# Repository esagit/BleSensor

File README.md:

# BLE Sensor Module
BLE sensor module development version for different sensors

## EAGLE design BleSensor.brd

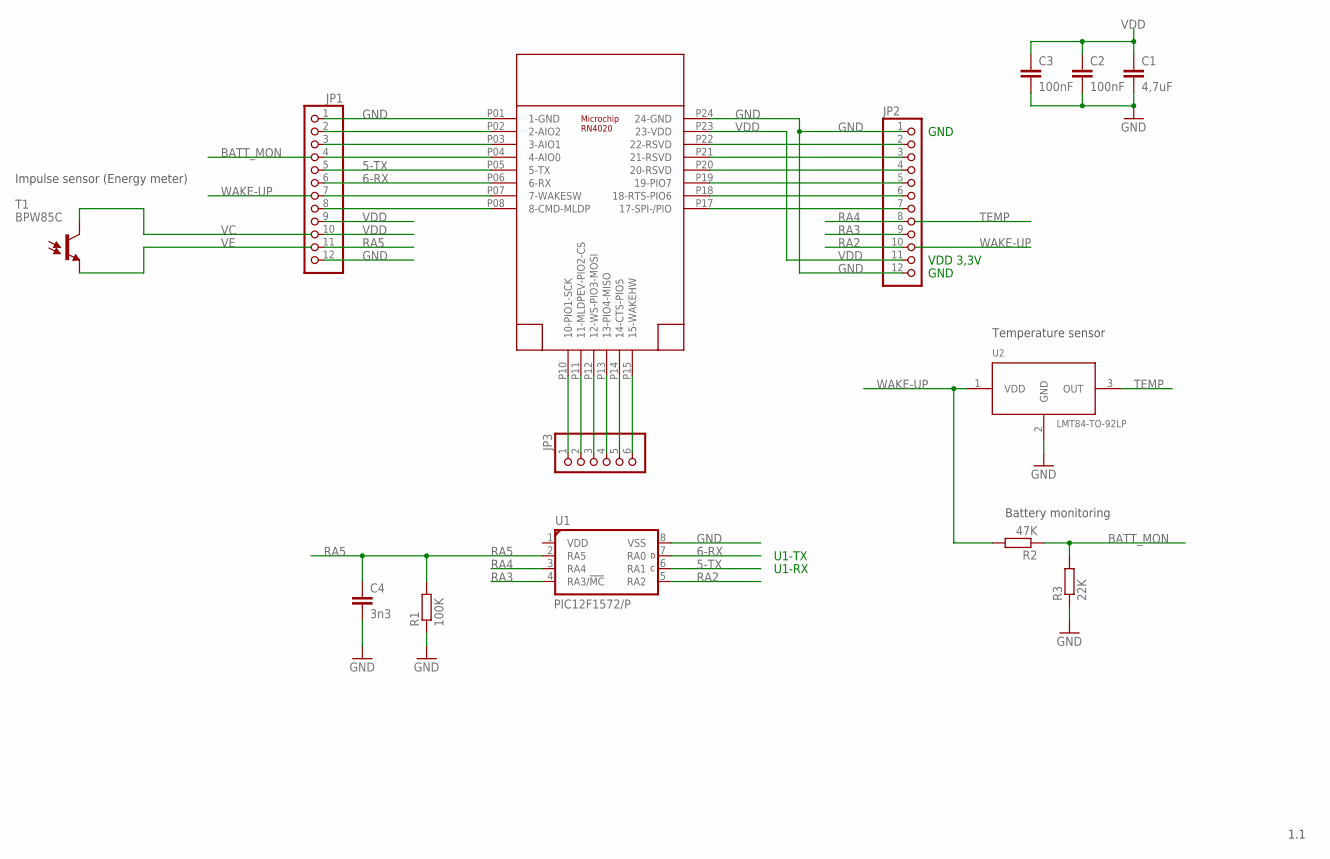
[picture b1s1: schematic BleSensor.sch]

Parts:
C1: 4,7uF; C2.5-3
C2, C3: 100nF; C1206
C4: 3n3; C1206
JP1, JP2: PINHD-1X12; 1X12
JP3: PINHD-1X6; 1X06
R1: 100K; M1206
R2: 47K; M1206
R3: 22K; M1206
T1: BPW85C; LED3MM
U1: PIC12F1572/P; DIL8-P
U2: LMT84-TO-92LP; TO92-LP
U$1: RN4020; RN4020SMD

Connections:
5-TX: JP1.5, U1.6 (RA1), U$1.P05 (5-TX)
6-RX: JP1.6, U1.7 (RA0), U$1.P06 (6-RX)
BATT_MON: JP1.4, R2.1, R3.2, U$1.P04 (4-AIO0)
GND: C1.2, C2.2, C3.2, C4.2, JP1.1, JP1.12, JP2.1, JP2.12, R1.1, R3.1, U1.8 (VSS), U2.2 (GND), U$1.P01 (1-GND), U$1.P24 (24-GND)
unnamed: JP1.8, U$1.P08 (8-CMD-MLDP)
unnamed: JP2.2, U$1.P22 (22-RSVD)
unnamed: JP2.3, U$1.P21 (21-RSVD)
unnamed: JP2.4, U$1.P20 (20-RSVD)
unnamed: JP2.5, U$1.P19 (19-PIO7)
unnamed: JP2.6, U$1.P18 (18-RTS-PIO6)
unnamed: JP2.7, U$1.P17 (17-SPI-/PIO)
unnamed: JP1.2, U$1.P02 (2-AIO2)
unnamed: JP1.3, U$1.P03 (3-AIO1)
unnamed: JP3.1, U$1.P10 (10-PIO1-SCK)
unnamed: JP3.2, U$1.P11 (11-MLDPEV-PIO2-CS)
unnamed: JP3.3, U$1.P12 (12-WS-PIO3-MOSI)
unnamed: JP3.4, U$1.P13 (13-PIO4-MISO)
unnamed: JP3.5, U$1.P14 (14-CTS-PIO5)
unnamed: JP3.6, U$1.P15 (15-WAKEHW)
RA2: JP1.7, JP2.10, U1.5 (RA2), U$1.P07 (7-WAKESW)
RA3: JP2.9, U1.4 (RA3/!MC!)
RA4: JP2.8, U1.3 (RA4)
RA5: C4.1, JP1.11, R1.2, U1.2 (RA5)
TEMP: U2.3 (OUT)
VC: T1.K (C)
VDD: C1.1, C2.1, C3.1, JP1.9, JP1.10, JP2.11, U$1.P23 (23-VDD)
VE: T1.A (E)
WAKE-UP: R2.2, U2.1 (VDD)

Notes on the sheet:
GND
VDD 3,3V
U1-TX
U1-RX
1.1
Temperature sensor
Impulse sensor (Energy meter)
Battery monitoring

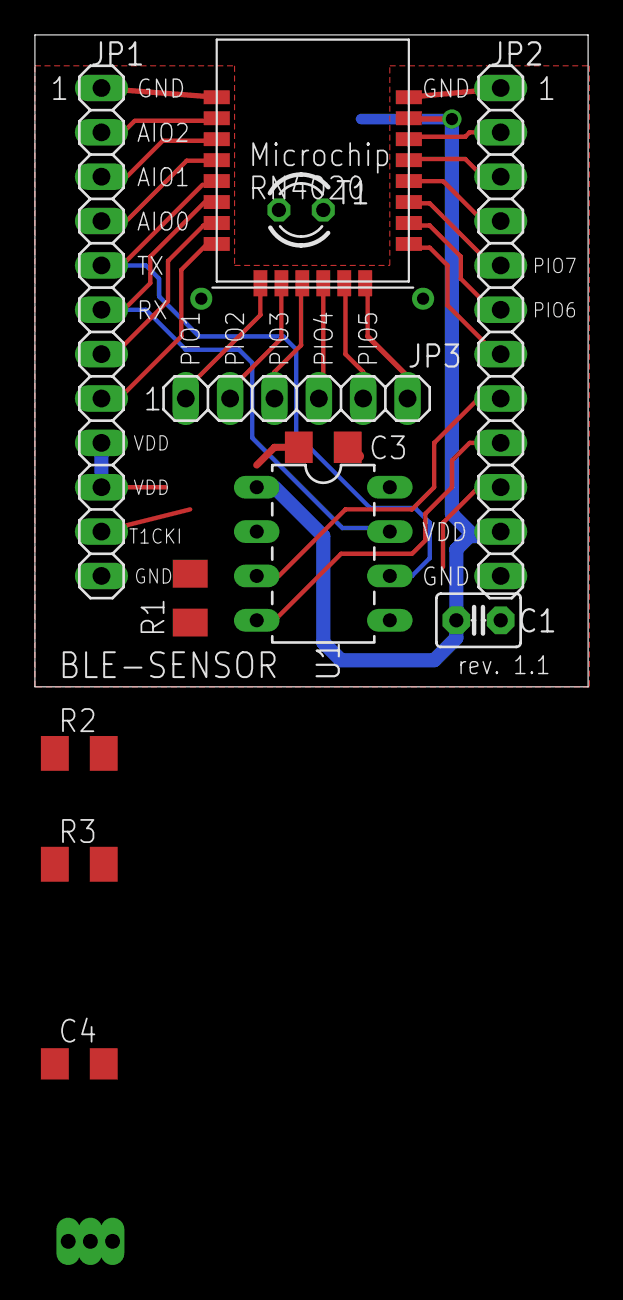
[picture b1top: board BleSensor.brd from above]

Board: 2 copper layers, 31.7 x 37.3 mm, 14 parts (1 on the bottom side), 25 nets.

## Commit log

2017-10-20 :boom::camel: Added .gitattributes & .gitignore files
2017-10-20 Initial Commit
    Initial Commit
2017-10-20 Added sensors
    Added sensors
2017-10-20 Updated .pdf file
    Updated .pdf file
2017-10-28 Fixed sensor inputs, added pdf Bitscope BLE Sensor pics
    Fixed sensor inputs, added pdf Bitscope BLE Sensor pics
2017-10-28 Updatetd BleSensor_sch.pdf
    Updatetd BleSensor_sch.pdf
2017-10-28 Updated BitScope BLE Sensor.pdf
    Updated BitScope BLE Sensor.pdf
